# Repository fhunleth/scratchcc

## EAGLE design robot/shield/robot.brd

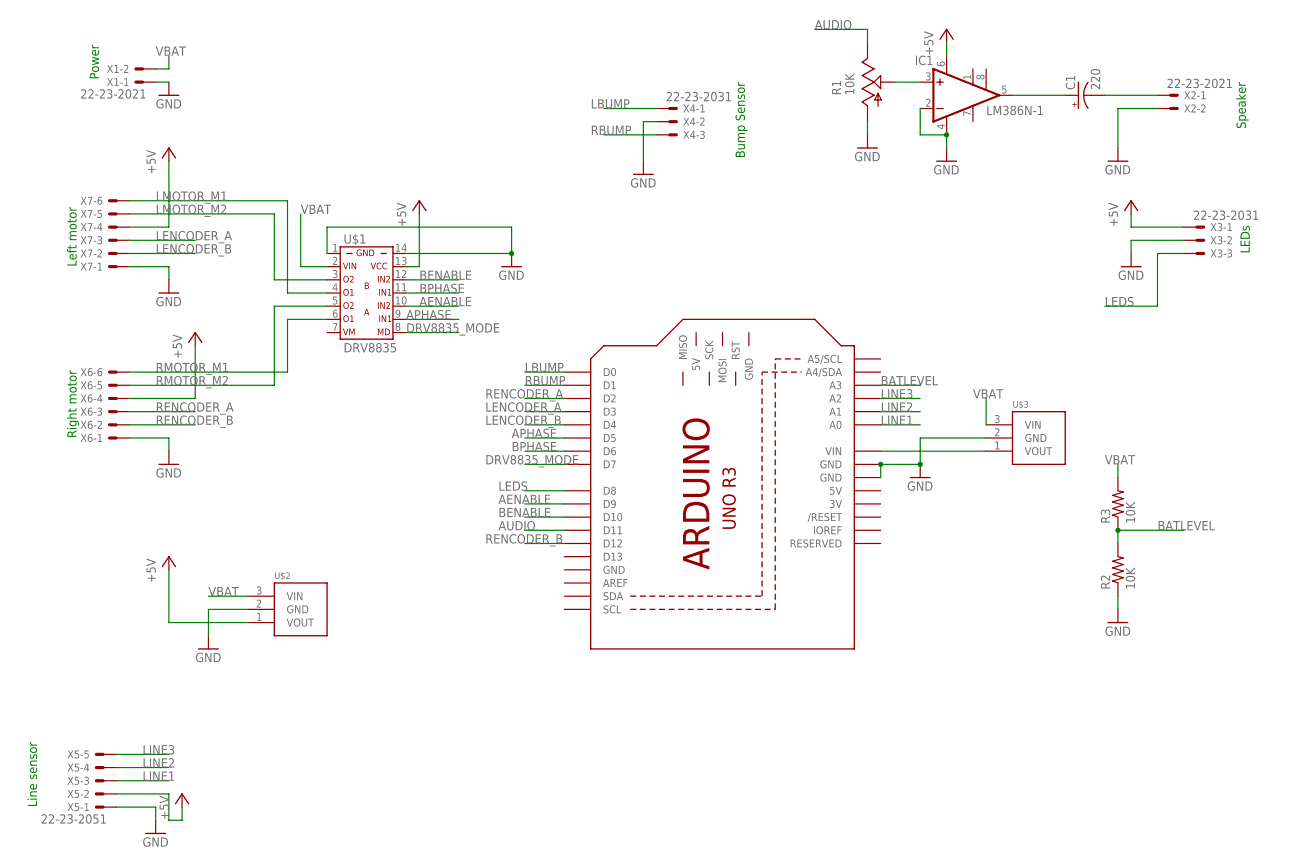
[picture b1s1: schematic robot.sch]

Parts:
C1: 220; E2,5-7
IC1: LM386N-1; DIL08
M2: ARDUINO_R3_ICSP; ARDUINOR3_ICSP
R1: 10K; S64W
R2, R3: 10K; V234/12
U$1: DRV8835; DIL14
U$2: S7V7F5; POLOLU-REG
U$3: U3V12F9; POLOLU-REG
X1, X2: 22-23-2021
X3, X4: 22-23-2031
X5: 22-23-2051
X6, X7: 22-23-2061

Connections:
3V: M2.3V
5V: M2.5V
+5V: IC1.6 (VS), U$1.13, U$2.1 (VOUT), X3.1, X5.2, X6.4, X7.4
AENABLE: M2.D9, U$1.10
APHASE: M2.D5, U$1.9
AUDIO: M2.D11, R1.E
BATLEVEL: M2.A3, R2.2, R3.1
BENABLE: M2.D10, U$1.12
BPHASE: M2.D6, U$1.11
DRV8835_MODE: M2.D7, U$1.8
GND: IC1.2 (-IN), IC1.4 (GND), M2.GND, M2.GND@1 (GND), M2.GND@3 (GND), R1.A, R2.1, U$1.1, U$1.14, U$2.2 (GND), U$3.2 (GND), X1.1, X2.2, X3.2, X4.2, X5.1, X6.1, X7.1
LBUMP: M2.D0, X4.1
LEDS: M2.D8, X3.3
LENCODER_A: M2.D3, X7.3
LENCODER_B: M2.D4, X7.2
LINE1: M2.A0, X5.3
LINE2: M2.A1, X5.4
LINE3: M2.A2, X5.5
LMOTOR_M1: U$1.4, X7.6
LMOTOR_M2: U$1.3, X7.5
unnamed: M2.VIN, U$3.1 (VOUT)
unnamed: C1.+, IC1.5 (OUT)
unnamed: IC1.3 (+IN), R1.S
unnamed: C1.-, X2.1
RBUMP: M2.D1, X4.3
RENCODER_A: M2.D2, X6.3
RENCODER_B: M2.D12, X6.2
RMOTOR_M1: U$1.6, X6.6
RMOTOR_M2: U$1.5, X6.5
VBAT: R3.2, U$1.2, U$2.3 (VIN), U$3.3 (VIN), X1.2

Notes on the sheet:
Left motor
Right motor
Speaker
LEDs
Line sensor
Power
Bump Sensor

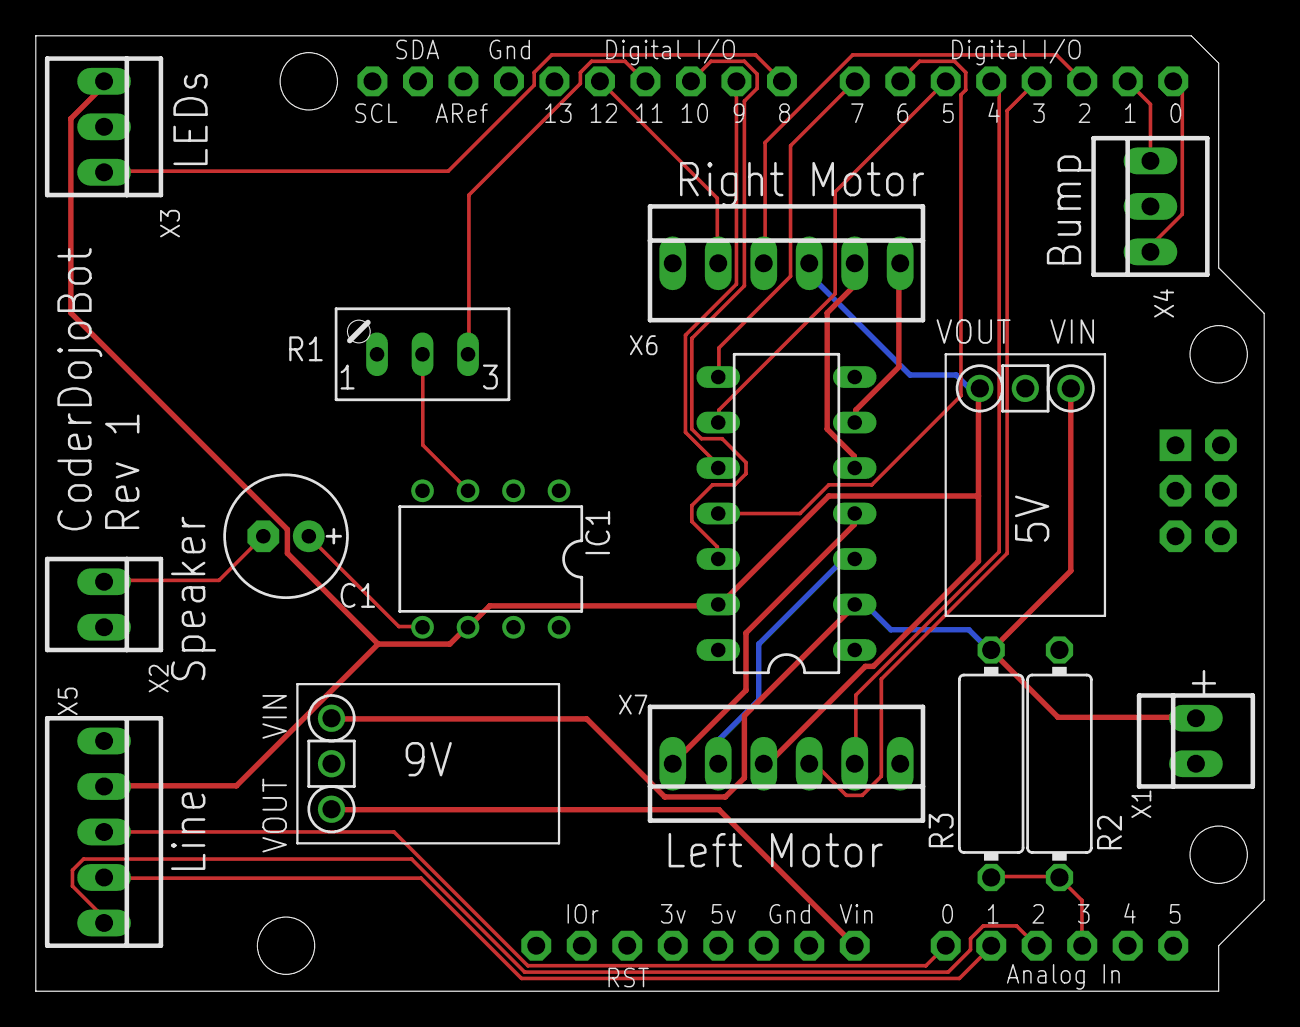
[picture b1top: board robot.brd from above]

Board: 2 copper layers, 68.6 x 53.3 mm, 16 parts (0 on the bottom side), 28 nets.

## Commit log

2014-06-21 Battery holder updates and side fix
2014-06-22 Add hole to push battery out; update pdfs
2014-07-04 Added whisker sensor mounts
2014-07-06 Add shield schematics and layout
2014-07-09 Various fixes after laser cutting first pieces
2014-07-09 Add laser cutter notes
2014-07-09 Add note about xps cropping on laser cutter
2014-07-10 Make battery holder walls wider to prevent them from breaking
2014-07-11 Add dimension to printout to test scale on printouts
2014-07-11 Update pdfs to latest
2014-07-15 Changes made at UMD
    I think that these have all been made addressed and don't need to be
    merged.
2014-07-15 Update pin assignments; layout
2014-07-17 Updates to schematic and layout
2014-07-18 Board version that was sent to OSH Park
2014-09-02 Add some notes for when we respin the board
2014-09-10 Add more notes
